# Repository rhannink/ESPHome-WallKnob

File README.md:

# ESPHome WallKnob-C6

Wall-mounted ESPHome rotary controller based on ESP32-C6, designed for a European flush-mount box and a Busch-Jaeger SI front.

## Rev A — frozen design basis

- Round PCB: **Ø58 mm**, 1.6 mm, 2-layer
- Rotary encoder shaft exactly at PCB geometric center
- **ESP32-C6-MINI-1**
- **EC11** incremental rotary encoder with push switch
- **Mean Well IRM-01-3.3** isolated 230 VAC → 3.3 V supply
- Status LED
- Programming/test pads
- On-board mains fuse
- Three mechanical mounting points
- Target installation depth: **40 mm**
- Busch-Jaeger SI-compatible front using the original frame/knob plus a 3D-printed adapter

Front side: encoder, ESP32-C6, status LED and programming pads.  
Rear side: IRM-01-3.3, fuse and AC input connector.

Rev A deliberately has **no** expansion header, relay, sensor, buzzer, RGB LED or extra buttons.

> **Safety:** This design contains hazardous mains voltage. Creepage/clearance, fusing, enclosure, insulation, PCB material, assembly and final installation must be verified against the applicable standards before connection to 230 VAC.

## Repository layout

- `hardware/` — Rev A mechanical/electrical design data
- `firmware/` — ESPHome configuration
- `docs/` — design notes, bring-up and safety checklist

## Current status

Rev A project baseline is now committed. The next hardware step is schematic capture and PCB routing while preserving the frozen mechanical constraints above.

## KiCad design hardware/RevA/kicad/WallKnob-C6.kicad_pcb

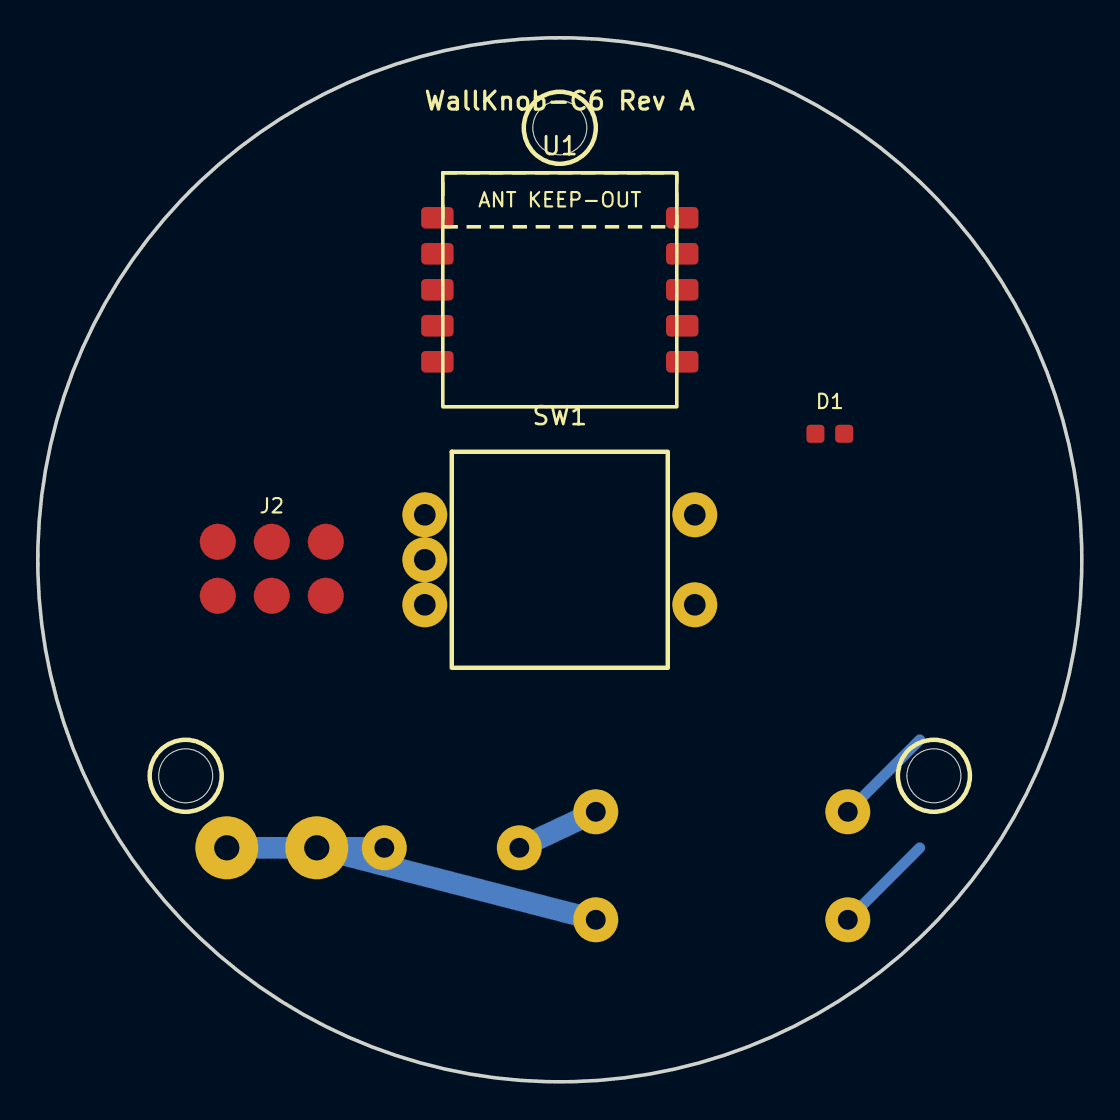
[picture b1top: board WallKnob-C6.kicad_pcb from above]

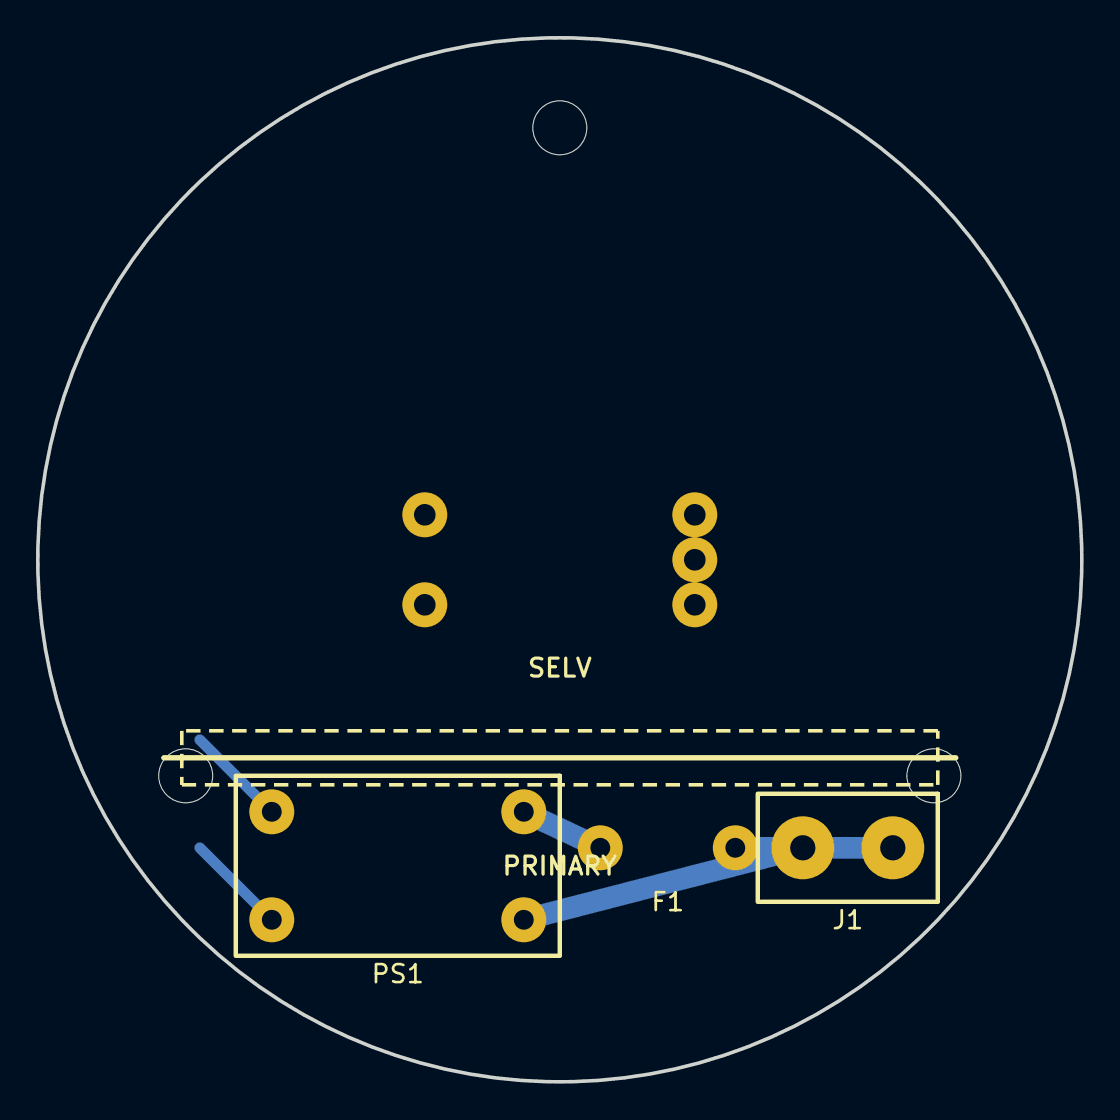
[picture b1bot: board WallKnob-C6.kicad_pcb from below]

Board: 2 copper layers, 58.0 x 58.0 mm, 10 parts (3 on the bottom side), 13 nets.

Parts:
D1: LED_0603
F1: FUSE_THT_CUSTOM
H1: MountingHole_1
H2: MountingHole_2
H3: MountingHole_3
J1: AC_IN_2P_CUSTOM
J2: TESTPADS_6
PS1: IRM-01-3.3 VERIFY FOOTPRINT; IRM-01-3.3_CUSTOM_VERIFY
SW1: EC11+PUSH; EC11_CUSTOM
U1: ESP32-C6-MINI-1; ESP32-C6-MINI-1_CUSTOM

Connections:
+3V3: J2.1, PS1.+V, U1.1
BOOT: J2.6, U1.8
EN: J2.5, U1.3
ENC_A: SW1.A, U1.4
ENC_B: SW1.B, U1.5
ENC_SW: SW1.S1, U1.6
GND: D1.2, J2.2, PS1.-V, SW1.C, SW1.S2, U1.2
LED: D1.1, U1.7
L_FUSED: F1.2, PS1.AC/L
L_IN: F1.1, J1.1
N_IN: J1.2, PS1.AC/N
UART_RX: J2.4, U1.10
UART_TX: J2.3, U1.9
